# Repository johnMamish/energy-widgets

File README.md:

Framework / toolkit for making widgets powered by UI actions, focused on example applications.

Key points:

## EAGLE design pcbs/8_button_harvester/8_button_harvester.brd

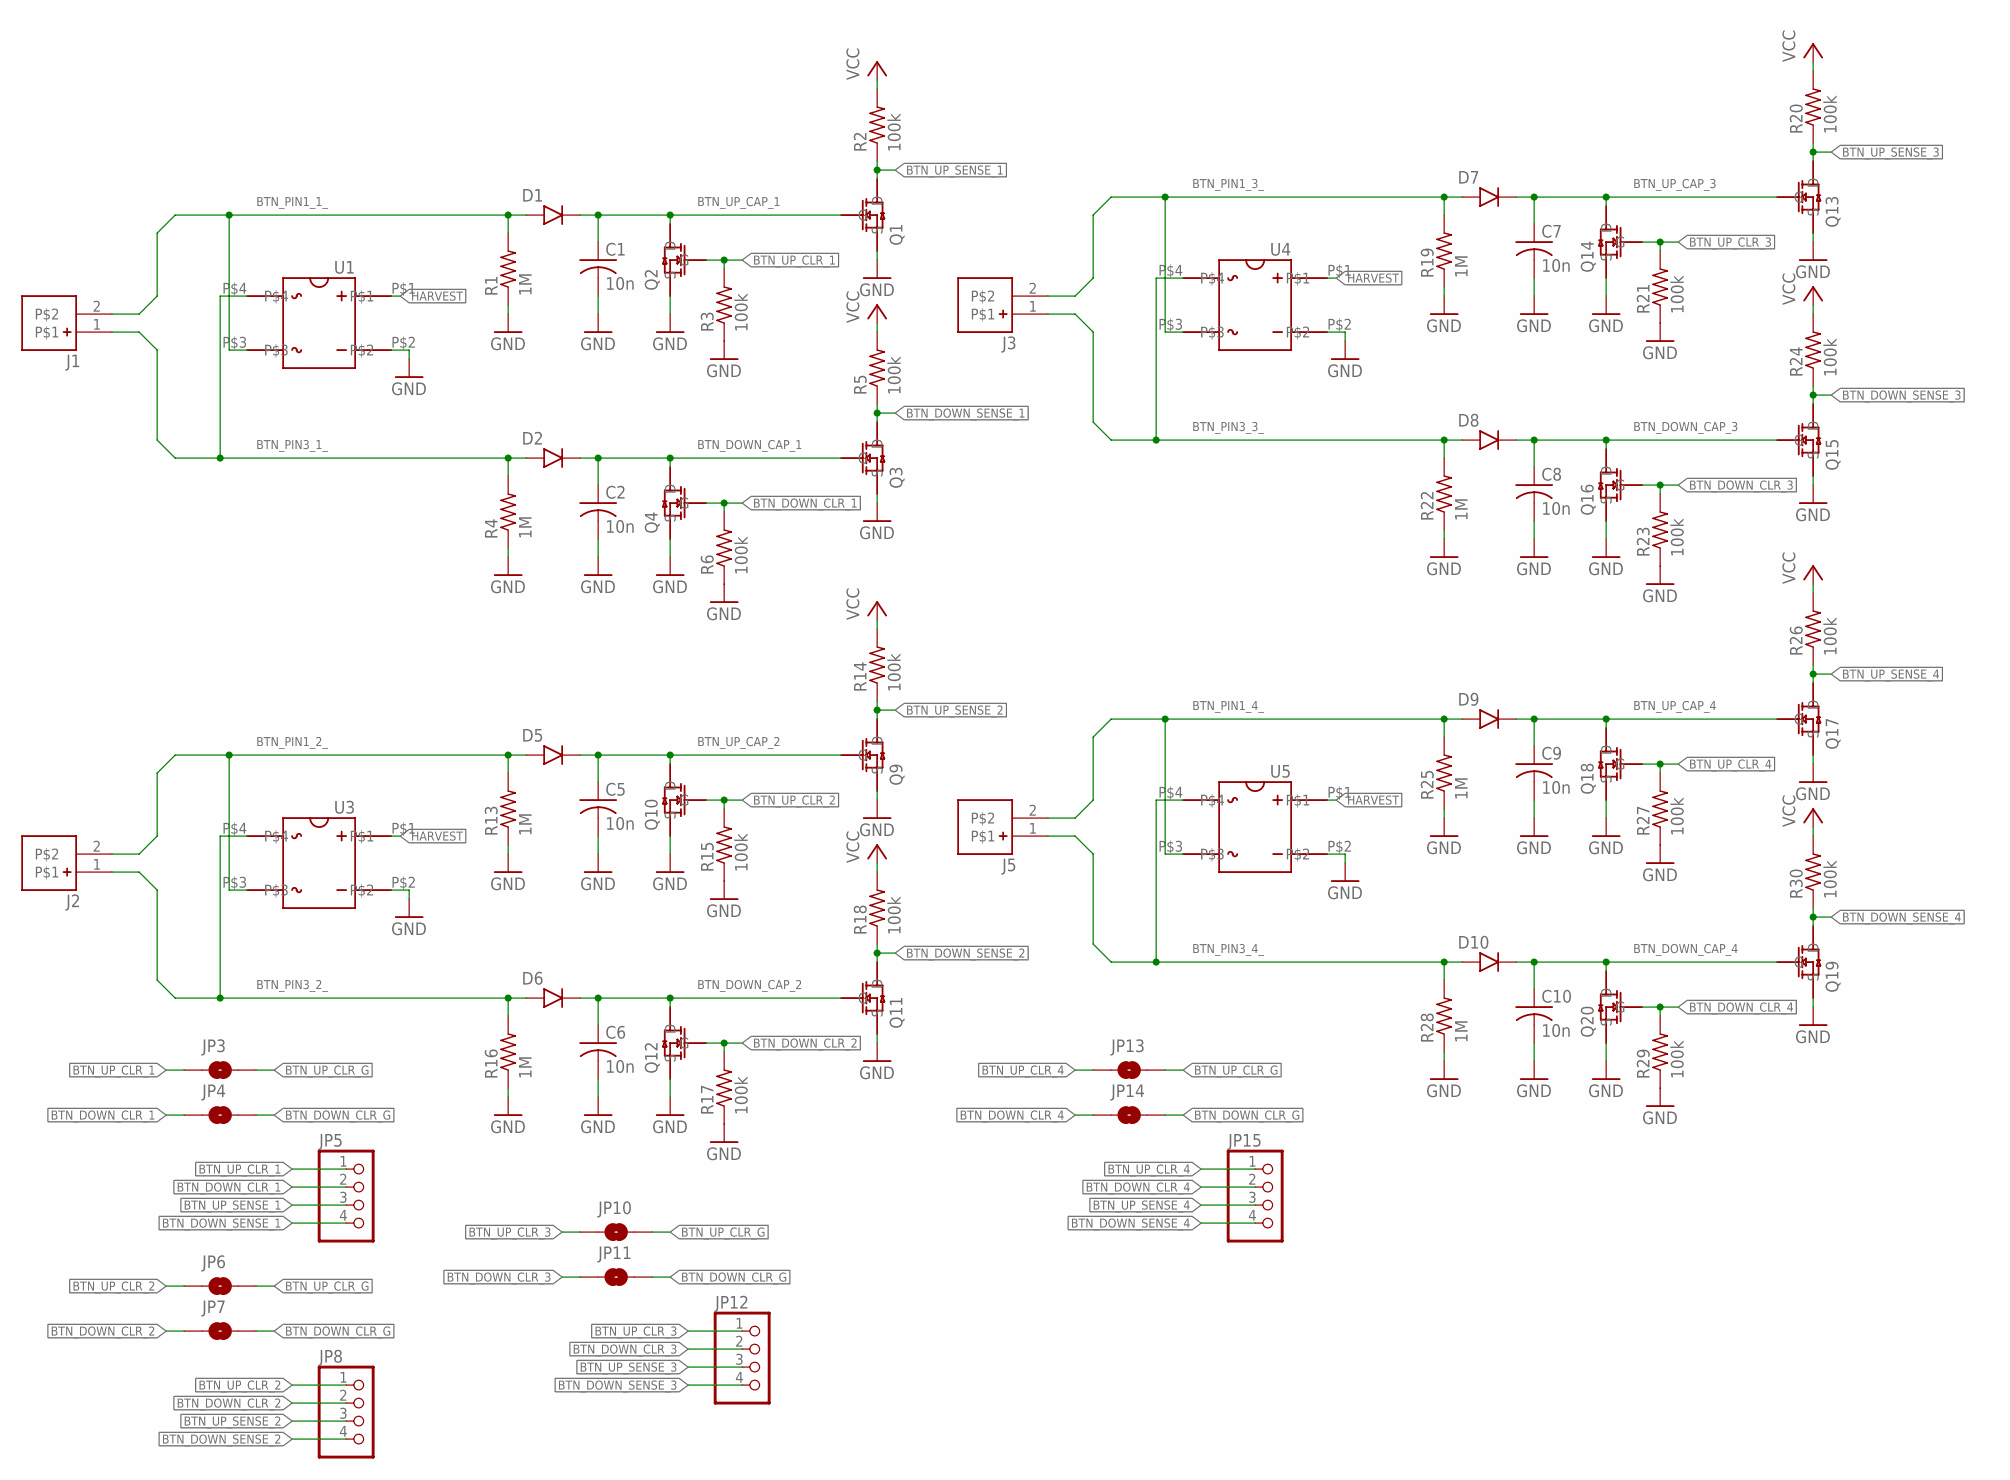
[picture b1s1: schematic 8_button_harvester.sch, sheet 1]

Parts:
C1, C2, C5, C6, C7, C8, C9, C10: 10n; C0402
D1, D2, D5, D6, D7, D8, D9, D10: DFLU1200
J1, J2, J3, J5: S2B-PH-SM4-TB
JP3, JP4, JP6, JP7, JP10, JP11, JP13, JP14: JUMPER-SMT_2_NO_NO-SILK; SMT-JUMPER_2_NO_NO-SILK
JP5, JP8, JP12, JP15: PINHD-1X4; 1X04
Q1, Q3, Q9, Q11, Q13, Q15, Q17, Q19: 2N7002K-7
Q2, Q4, Q10, Q12, Q14, Q16, Q18, Q20: BSS138K
R1, R4, R13, R16, R19, R22, R25, R28: 1M; R0402
R2, R3, R5, R6, R14, R15, R17, R18, R20, R21, R23, R24, R26, R27, R29, R30: 100k; R0402
U1, U3, U4, U5: CDBHD140L-G; CDBHDXX0L-G

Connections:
BTN_DOWN_CAP_1: C2.1, D2.K, Q3.G, Q4.D
BTN_DOWN_CAP_2: C6.1, D6.K, Q11.G, Q12.D
BTN_DOWN_CAP_3: C8.1, D8.K, Q15.G, Q16.D
BTN_DOWN_CAP_4: C10.1, D10.K, Q19.G, Q20.D
BTN_DOWN_CLR_1: JP4.1, JP5.2, Q4.G, R6.2
BTN_DOWN_CLR_2: JP7.1, JP8.2, Q12.G, R17.2
BTN_DOWN_CLR_3: JP11.1, JP12.2, Q16.G, R23.2
BTN_DOWN_CLR_4: JP14.1, JP15.2, Q20.G, R29.2
BTN_DOWN_CLR_G: JP4.2, JP7.2, JP11.2, JP14.2; also elsewhere on the board
BTN_DOWN_SENSE_1: JP5.4, Q3.D, R5.1
BTN_DOWN_SENSE_2: JP8.4, Q11.D, R18.1
BTN_DOWN_SENSE_3: JP12.4, Q15.D, R24.1
BTN_DOWN_SENSE_4: JP15.4, Q19.D, R30.1
BTN_PIN1_1_: D1.A, J1.2, R1.2, U1.P$3
BTN_PIN1_2_: D5.A, J2.2, R13.2, U3.P$3
BTN_PIN1_3_: D7.A, J3.2, R19.2, U4.P$3
BTN_PIN1_4_: D9.A, J5.2, R25.2, U5.P$3
BTN_PIN3_1_: D2.A, J1.1, R4.2, U1.P$4
BTN_PIN3_2_: D6.A, J2.1, R16.2, U3.P$4
BTN_PIN3_3_: D8.A, J3.1, R22.2, U4.P$4
BTN_PIN3_4_: D10.A, J5.1, R28.2, U5.P$4
BTN_UP_CAP_1: C1.1, D1.K, Q1.G, Q2.D
BTN_UP_CAP_2: C5.1, D5.K, Q9.G, Q10.D
BTN_UP_CAP_3: C7.1, D7.K, Q13.G, Q14.D
BTN_UP_CAP_4: C9.1, D9.K, Q17.G, Q18.D
BTN_UP_CLR_1: JP3.1, JP5.1, Q2.G, R3.2
BTN_UP_CLR_2: JP6.1, JP8.1, Q10.G, R15.2
BTN_UP_CLR_3: JP10.1, JP12.1, Q14.G, R21.2
BTN_UP_CLR_4: JP13.1, JP15.1, Q18.G, R27.2
BTN_UP_CLR_G: JP3.2, JP6.2, JP10.2, JP13.2; also elsewhere on the board
BTN_UP_SENSE_1: JP5.3, Q1.D, R2.1
BTN_UP_SENSE_2: JP8.3, Q9.D, R14.1
BTN_UP_SENSE_3: JP12.3, Q13.D, R20.1
BTN_UP_SENSE_4: JP15.3, Q17.D, R26.1
GND: C1.2, C2.2, C5.2, C6.2, C7.2, C8.2, C9.2, C10.2, Q1.S, Q2.S, Q3.S, Q4.S, Q9.S, Q10.S, Q11.S, Q12.S, Q13.S, Q14.S, Q15.S, Q16.S, Q17.S, Q18.S, Q19.S, Q20.S, R1.1, R3.1, R4.1, R6.1, R13.1, R15.1, R16.1, R17.1, R19.1, R21.1, R22.1, R23.1, R25.1, R27.1, R28.1, R29.1, U1.P$2, U3.P$2, U4.P$2, U5.P$2; also elsewhere on the board
HARVEST: U1.P$1, U3.P$1, U4.P$1, U5.P$1; also elsewhere on the board
VCC: R2.2, R5.2, R14.2, R18.2, R20.2, R24.2, R26.2, R30.2; also elsewhere on the board

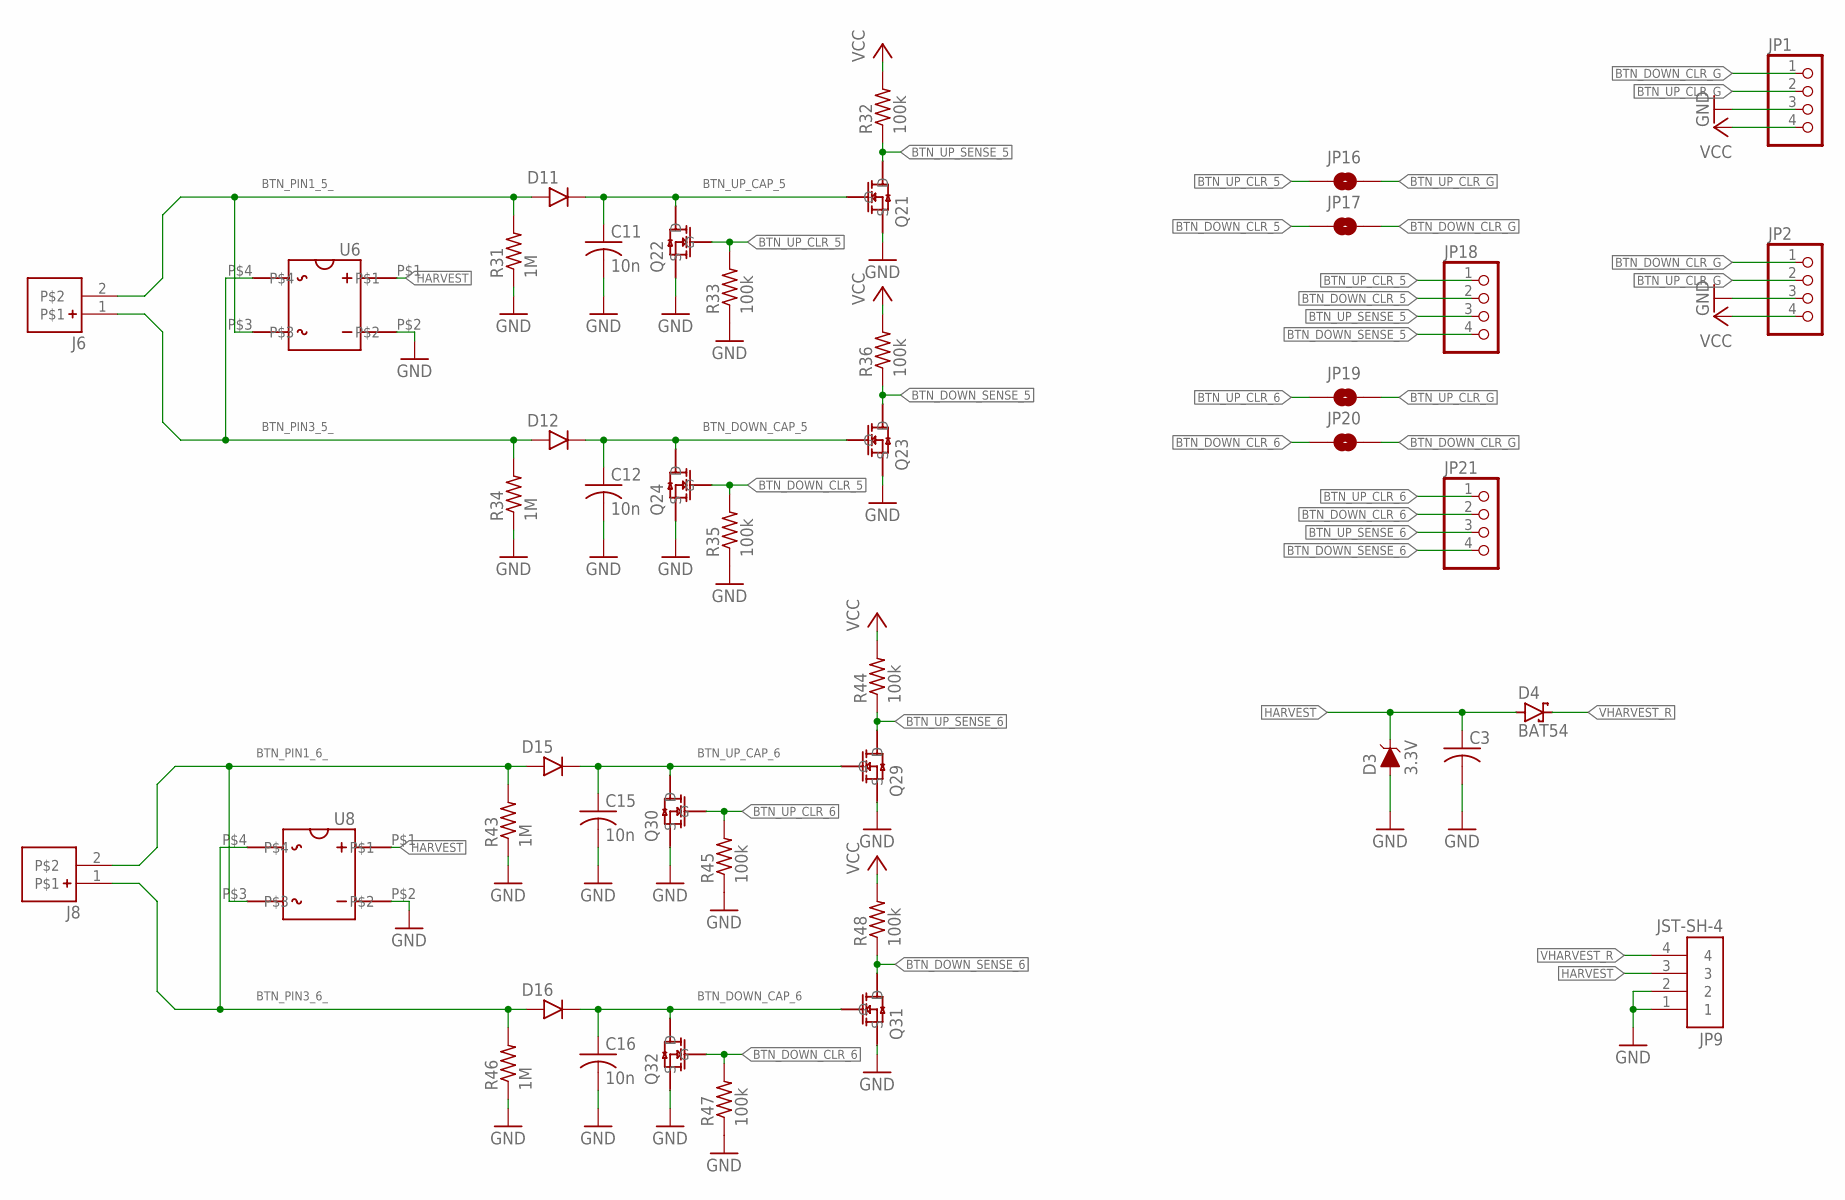
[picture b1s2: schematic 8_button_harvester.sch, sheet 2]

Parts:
C3: C-USC0805; C0805
C11, C12, C15, C16: 10n; C0402
D3: 3.3V; SOD-323
D4: BAT54; SOT23
D11, D12, D15, D16: DFLU1200
J6, J8: S2B-PH-SM4-TB
JP1, JP2, JP18, JP21: PINHD-1X4; 1X04
JP9: JST-SH-4
JP16, JP17, JP19, JP20: JUMPER-SMT_2_NO_NO-SILK; SMT-JUMPER_2_NO_NO-SILK
Q21, Q23, Q29, Q31: 2N7002K-7
Q22, Q24, Q30, Q32: BSS138K
R31, R34, R43, R46: 1M; R0402
R32, R33, R35, R36, R44, R45, R47, R48: 100k; R0402
U6, U8: CDBHD140L-G; CDBHDXX0L-G

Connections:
BTN_DOWN_CAP_5: C12.1, D12.K, Q23.G, Q24.D
BTN_DOWN_CAP_6: C16.1, D16.K, Q31.G, Q32.D
BTN_DOWN_CLR_5: JP17.1, JP18.2, Q24.G, R35.2
BTN_DOWN_CLR_6: JP20.1, JP21.2, Q32.G, R47.2
BTN_DOWN_CLR_G: JP1.1, JP2.1, JP17.2, JP20.2; also elsewhere on the board
BTN_DOWN_SENSE_5: JP18.4, Q23.D, R36.1
BTN_DOWN_SENSE_6: JP21.4, Q31.D, R48.1
BTN_PIN1_5_: D11.A, J6.2, R31.2, U6.P$3
BTN_PIN1_6_: D15.A, J8.2, R43.2, U8.P$3
BTN_PIN3_5_: D12.A, J6.1, R34.2, U6.P$4
BTN_PIN3_6_: D16.A, J8.1, R46.2, U8.P$4
BTN_UP_CAP_5: C11.1, D11.K, Q21.G, Q22.D
BTN_UP_CAP_6: C15.1, D15.K, Q29.G, Q30.D
BTN_UP_CLR_5: JP16.1, JP18.1, Q22.G, R33.2
BTN_UP_CLR_6: JP19.1, JP21.1, Q30.G, R45.2
BTN_UP_CLR_G: JP1.2, JP2.2, JP16.2, JP19.2; also elsewhere on the board
BTN_UP_SENSE_5: JP18.3, Q21.D, R32.1
BTN_UP_SENSE_6: JP21.3, Q29.D, R44.1
GND: C3.2, C11.2, C12.2, C15.2, C16.2, D3.A, JP1.3, JP2.3, JP9.1, JP9.2, Q21.S, Q22.S, Q23.S, Q24.S, Q29.S, Q30.S, Q31.S, Q32.S, R31.1, R33.1, R34.1, R35.1, R43.1, R45.1, R46.1, R47.1, U6.P$2, U8.P$2; also elsewhere on the board
HARVEST: C3.1, D3.C, D4.1 (A), JP9.3, U6.P$1, U8.P$1; also elsewhere on the board
VCC: JP1.4, JP2.4, R32.2, R36.2, R44.2, R48.2; also elsewhere on the board
VHARVEST_R: D4.3 (C), JP9.4

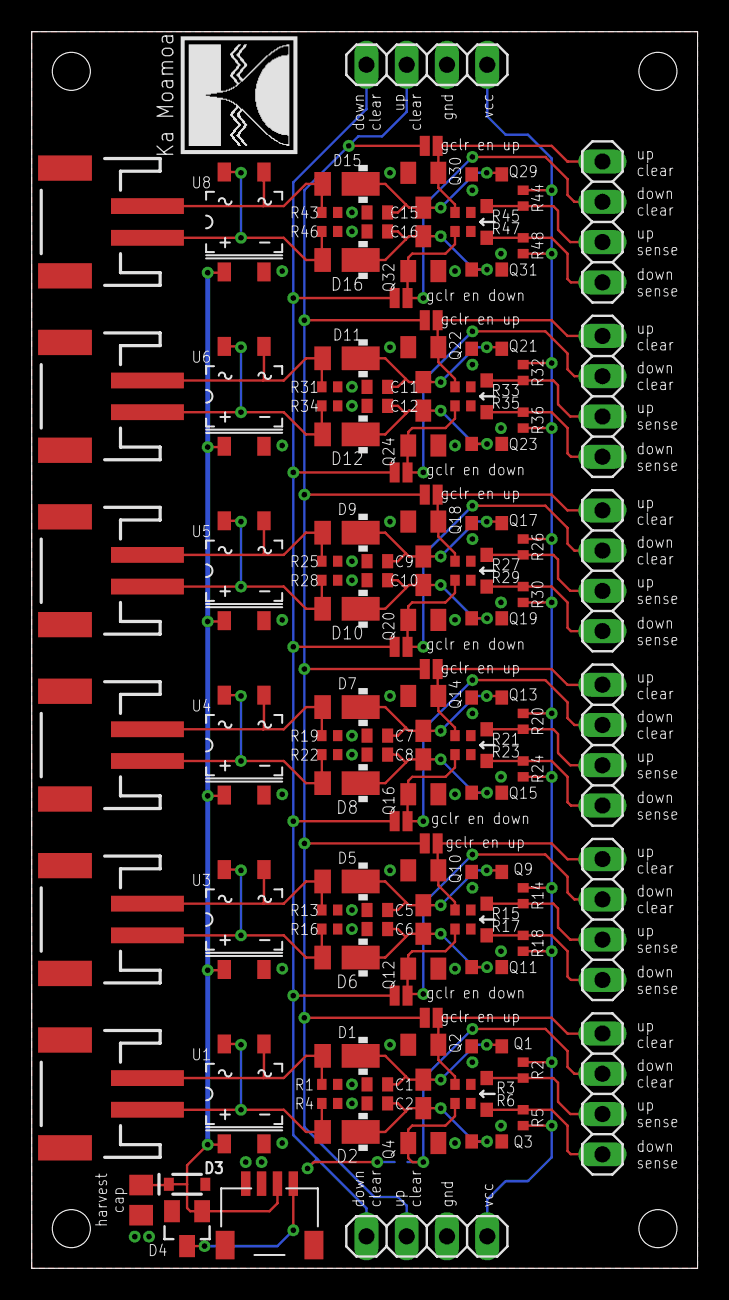
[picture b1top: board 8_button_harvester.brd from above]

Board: 2 copper layers, 42.0 x 78.0 mm, 120 parts (1 on the bottom side), 54 nets.

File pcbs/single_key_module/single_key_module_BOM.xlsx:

Digikey P/N | Manufacturer P/N | Quantity | Reference designator | Value | Device | Package | Description
 | N/A | 1 | AF1 | BUTTON-MOUNT | BUTTON-MOUNT | BUTTON-MOUNT
 | AFIG-0007 | 1
 | 878580002 | 1
 | C0402C103J3RACTU | 2 | C1, C2 | 10n | C-USC0402 | C0402 | CAPACITOR, American symbol
 | DFLU1200 | 2 | D1, D2 |  | DFLU1200 | DFLU1200
 | 61300411121 | 2 | headers |  |  |  | PIN HEADER
 | 2N7002K-7 | 2 | Q1, Q3 | 2N7002K-7 | 2N7002K-7 | 2N7002K-7
 | BSS138K | 2 | Q2, Q4 | BSS138K | BSS138K | BSS138K
 | ERJ-2GEJ105X | 2 | R1, R4 | 1M | R-US_R0402 | R0402 | RESISTOR, American symbol
 | ERJ-2GEJ104X | 4 | R2, R3, R5, R6 | 100k | R-US_R0402 | R0402 | RESISTOR, American symbol
 | CDBHD140L-G | 1 | U1 | CDBHD140L-G | CDBHD140L-G | CDBHDXX0L-G

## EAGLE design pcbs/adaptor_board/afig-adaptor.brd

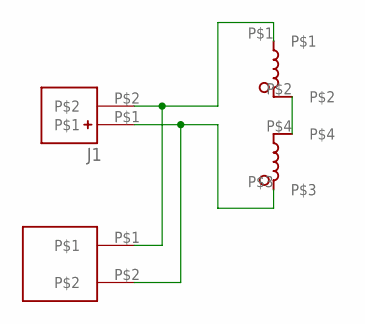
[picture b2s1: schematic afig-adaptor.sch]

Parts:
J1: B2B-PH-SM4-TB
U$1: AFIG-0007
U$2: 0878580002

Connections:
unnamed: U$1.P$2, U$1.P$4
unnamed: J1.P$1, U$1.P$3, U$2.P$2
unnamed: J1.P$2, U$1.P$1, U$2.P$1

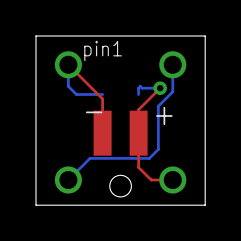
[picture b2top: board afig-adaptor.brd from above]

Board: 2 copper layers, 9.4 x 9.4 mm, 3 parts (1 on the bottom side), 3 nets.

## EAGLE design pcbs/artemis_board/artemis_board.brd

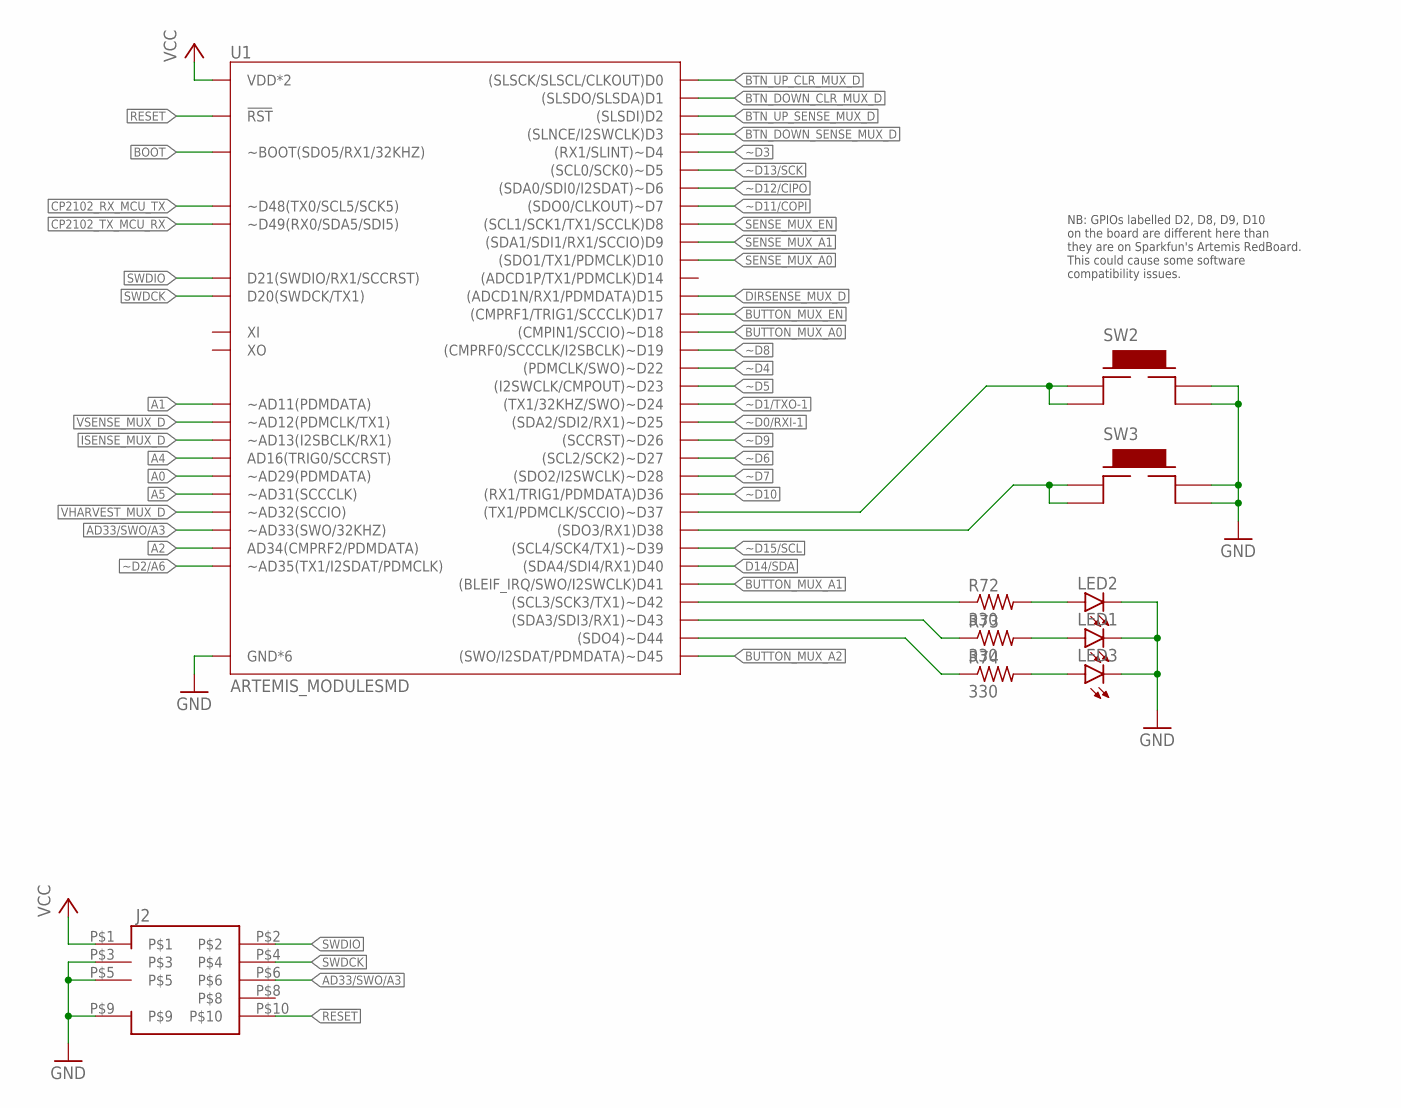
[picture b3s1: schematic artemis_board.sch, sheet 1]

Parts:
J2: FTSH-105-01-F-DV-007-K-P
LED1, LED2, LED3: LEDCHIP-LED0603; CHIP-LED0603; MFR_PN BR1111C-TR
R72, R73, R74: 330; R0402; MFR_PN RC0402FR-07330RL
SW2, SW3: TE_FSM4JSMA; TE_FSMJSMA
U1: ARTEMIS_MODULESMD; ARTEMIS_FP; MFR_PN WRL-15484

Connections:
!RESET: J2.P$10, U1.~RST (!RST); also elsewhere on the board
A0: U1.~AD29 (~AD29(PDMDATA)); also elsewhere on the board
A1: U1.~AD11 (~AD11(PDMDATA)); also elsewhere on the board
A2: U1.AD34 (AD34(CMPRF2/PDMDATA)); also elsewhere on the board
A4: U1.AD16 (AD16(TRIG0/SCCRST)); also elsewhere on the board
A5: U1.~AD31 (~AD31(SCCCLK)); also elsewhere on the board
AD33/SWO/A3: J2.P$6, U1.~AD33/SWO (~AD33(SWO/32KHZ)); also elsewhere on the board
BOOT: U1.BOOT (~BOOT(SDO5/RX1/32KHZ)); also elsewhere on the board
BTN_DOWN_CLR_MUX_D: U1.D1 ((SLSDO/SLSDA)D1); also elsewhere on the board
BTN_DOWN_SENSE_MUX_D: U1.D3 ((SLNCE/I2SWCLK)D3); also elsewhere on the board
BTN_UP_CLR_MUX_D: U1.D0 ((SLSCK/SLSCL/CLKOUT)D0); also elsewhere on the board
BTN_UP_SENSE_MUX_D: U1.D2 ((SLSDI)D2); also elsewhere on the board
BUTTON_MUX_A0: U1.~D18 ((CMPIN1/SCCIO)~D18); also elsewhere on the board
BUTTON_MUX_A1: U1.D41 ((BLEIF_IRQ/SWO/I2SWCLK)D41); also elsewhere on the board
BUTTON_MUX_A2: U1.~D45 ((SWO/I2SDAT/PDMDATA)~D45); also elsewhere on the board
BUTTON_MUX_EN: U1.D17 ((CMPRF1/TRIG1/SCCCLK)D17); also elsewhere on the board
CP2102_RX_MCU_TX: U1.TXO-0 (~D48(TX0/SCL5/SCK5)); also elsewhere on the board
CP2102_TX_MCU_RX: U1.RXI-0 (~D49(RX0/SDA5/SDI5)); also elsewhere on the board
D14/SDA: U1.D40 ((SDA4/SDI4/RX1)D40); also elsewhere on the board
DIRSENSE_MUX_D: U1.D15 ((ADCD1N/RX1/PDMDATA)D15); also elsewhere on the board
GND: J2.P$3, J2.P$5, J2.P$9, LED1.C, LED2.C, LED3.C, SW2.P$3, SW2.P$4, SW3.P$3, SW3.P$4, U1.GND@1 (GND*6), U1.GND@22 (GND*6), U1.GND@38 (GND*6), U1.GND@39 (GND*6), U1.GND@47 (GND*6), U1.GND@59 (GND*6); also elsewhere on the board
ISENSE_MUX_D: U1.~AD13 (~AD13(I2SBCLK/RX1)); also elsewhere on the board
unnamed: R72.1, U1.~D42 ((SCL3/SCK3/TX1)~D42)
unnamed: R73.1, U1.~D43 ((SDA3/SDI3/RX1)~D43)
unnamed: R74.1, U1.~D44 ((SDO4)~D44)
unnamed: LED2.A, R72.2
unnamed: LED1.A, R73.2
unnamed: LED3.A, R74.2
unnamed: SW2.P$1, SW2.P$2, U1.~D37 ((TX1/PDMCLK/SCCIO)~D37)
unnamed: SW3.P$1, SW3.P$2, U1.D38 ((SDO3/RX1)D38)
SENSE_MUX_A0: U1.D10 ((SDO1/TX1/PDMCLK)D10); also elsewhere on the board
SENSE_MUX_A1: U1.D9 ((SDA1/SDI1/RX1/SCCIO)D9); also elsewhere on the board
SENSE_MUX_EN: U1.D8 ((SCL1/SCK1/TX1/SCCLK)D8); also elsewhere on the board
SWDCK: J2.P$4, U1.SWDCK (D20(SWDCK/TX1))
SWDIO: J2.P$2, U1.SWDIO (D21(SWDIO/RX1/SCCRST))
VCC: J2.P$1, U1.VDD@36 (VDD*2), U1.VDD@37 (VDD*2); also elsewhere on the board
VHARVEST_MUX_D: U1.~AD32 (~AD32(SCCIO)); also elsewhere on the board
VSENSE_MUX_D: U1.~AD12 (~AD12(PDMCLK/TX1)); also elsewhere on the board
~D0/RXI-1: U1.~D25 ((SDA2/SDI2/RX1)~D25); also elsewhere on the board
~D1/TXO-1: U1.~D24 ((TX1/32KHZ/SWO)~D24); also elsewhere on the board
~D2/A6: U1.~AD35 (~AD35(TX1/I2SDAT/PDMCLK)); also elsewhere on the board
~D3: U1.~D4 ((RX1/SLINT)~D4); also elsewhere on the board
~D4: U1.~D22 ((PDMCLK/SWO)~D22); also elsewhere on the board
~D5: U1.~D23 ((I2SWCLK/CMPOUT)~D23); also elsewhere on the board
~D6: U1.~D27 ((SCL2/SCK2)~D27); also elsewhere on the board
~D7: U1.~D28 ((SDO2/I2SWCLK)~D28); also elsewhere on the board
~D8: U1.~D19 ((CMPRF0/SCCCLK/I2SBCLK)~D19); also elsewhere on the board
~D9: U1.~D26 ((SCCRST)~D26); also elsewhere on the board
~D10: U1.D36 ((RX1/TRIG1/PDMDATA)D36); also elsewhere on the board
~D11/COPI: U1.D7 ((SDO0/CLKOUT)~D7); also elsewhere on the board
~D12/CIPO: U1.~D6 ((SDA0/SDI0/I2SDAT)~D6); also elsewhere on the board
~D13/SCK: U1.~D5 ((SCL0/SCK0)~D5); also elsewhere on the board
~D15/SCL: U1.~D39 ((SCL4/SCK4/TX1)~D39); also elsewhere on the board

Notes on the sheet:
NB: GPIOs labelled D2, D8, D9, D10 on the board are different here than they are on Sparkfun's Artemis RedBoard. This could cause some software compatibility issues.

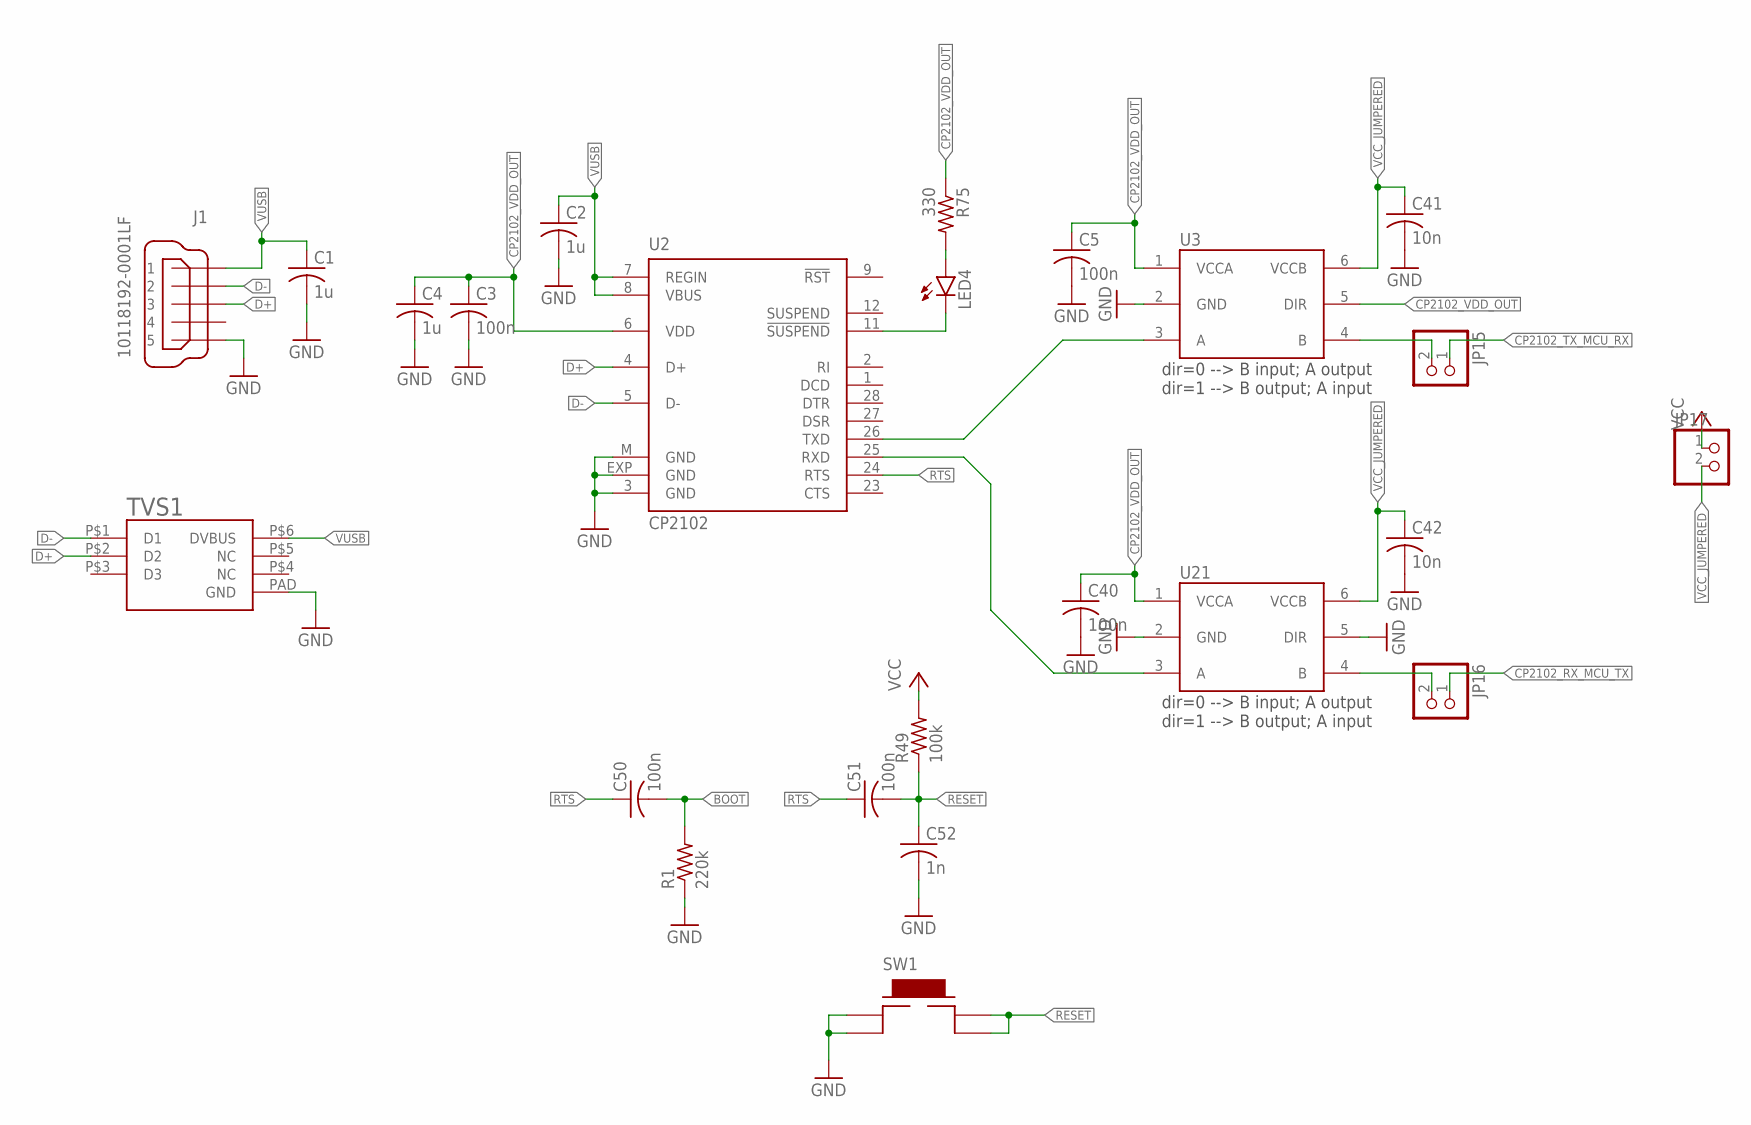
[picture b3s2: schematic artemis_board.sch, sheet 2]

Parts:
C1, C2, C4: 1u; C0402; MFR_PN CL05A105KO5NNNC
C3, C5, C40, C50, C51: 100n; C0402; MFR_PN CL05B104KO5NNNC
C41, C42: 10n; C0402; MFR_PN CL05B103KO5NNNC
C52: 1n; C0402; MFR_PN CL05B102KB5NNNC
J1: 10118192-0001LF
JP15, JP16, JP17: PINHD-1X2; 1X02
LED4: LEDCHIP-LED0603; CHIP-LED0603; MFR_PN BR1111C-TR
R1: 220k; R0402; MFR_PN RC0402FR-07220KL
R49: 100k; R0402; MFR_PN RC0402FR-07100KL
R75: 330; R0402; MFR_PN RC0402FR-07330RL
SW1: TE_FSM4JSMA; TE_FSMJSMA
TVS1: RCLAMP3654PAT; RCLAMP3654PATCT
U2: CP2102; MLP28; MFR_PN CP2102-GM
U3, U21: 74AXP1T45GWH; SOT65P210X110-6N

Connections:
!RESET: C51.2, C52.1, R49.1, SW1.P$3, SW1.P$4; also elsewhere on the board
!RTS: C50.1, C51.1, U2.24 (RTS)
BOOT: C50.2, R1.2; also elsewhere on the board
CP2102_RX_MCU_TX: JP16.1; also elsewhere on the board
CP2102_TX_MCU_RX: JP15.1; also elsewhere on the board
CP2102_VDD_OUT: C3.1, C4.1, C5.1, C40.1, R75.1, U2.6 (VDD), U3.1 (VCCA), U3.5 (DIR), U21.1 (VCCA)
D+: J1.3, TVS1.P$2 (D2), U2.4 (D+)
D-: J1.2, TVS1.P$1 (D1), U2.5 (D-)
GND: C1.2, C2.2, C3.2, C4.2, C5.2, C40.2, C41.2, C42.2, C52.2, J1.5, R1.1, SW1.P$1, SW1.P$2, TVS1.PAD (GND), U2.3 (GND), U2.EXP (GND), U2.M (GND), U3.2 (GND), U21.2 (GND), U21.5 (DIR); also elsewhere on the board
unnamed: LED4.A, R75.2
unnamed: JP15.2, U3.4 (B)
unnamed: JP16.2, U21.4 (B)
unnamed: LED4.C, U2.11 (!SUSPEND)
RXD_3V3: U2.25 (RXD), U21.3 (A)
TXD_3V3: U2.26 (TXD), U3.3 (A)
VCC: JP17.1, R49.2; also elsewhere on the board
VCC_JUMPERED: C41.1, C42.1, JP17.2, U3.6 (VCCB), U21.6 (VCCB)
VUSB: C1.1, C2.1, J1.1, TVS1.P$6 (DVBUS), U2.7 (REGIN), U2.8 (VBUS); also elsewhere on the board

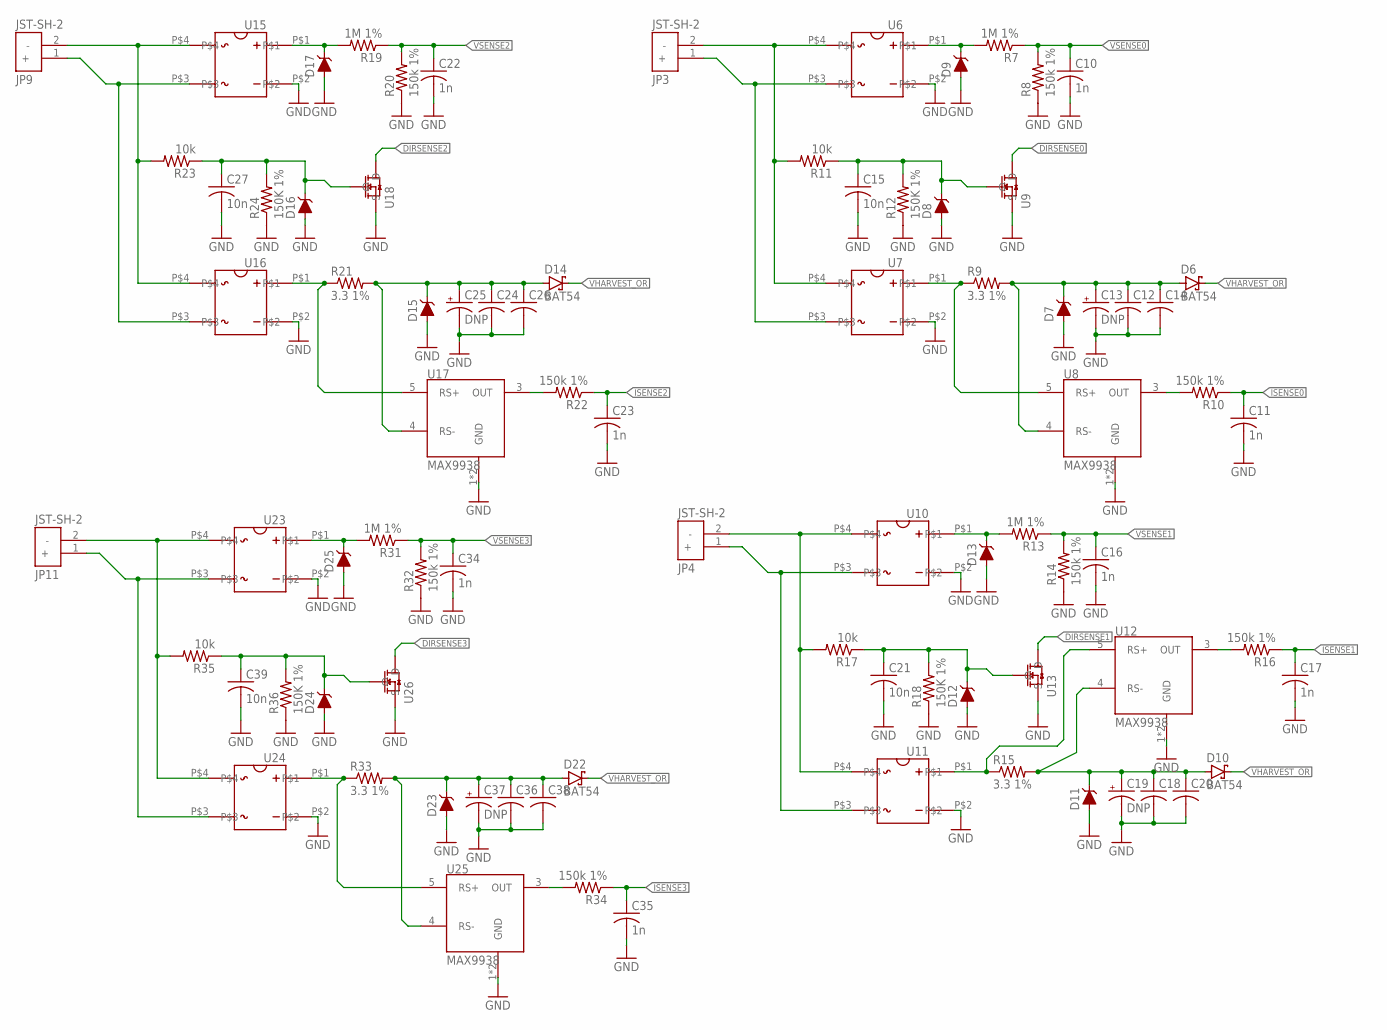
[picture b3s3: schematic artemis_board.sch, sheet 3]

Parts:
C10, C11, C16, C17, C22, C23, C34, C35: 1n; C0402; MFR_PN CL05B102KB5NNNC
C12, C14, C18, C20, C24, C26, C36, C38: C-USC1206; C1206; MFR_PN C3216X5R1E476M160AC
C13, C19, C25, C37: DNP; E2,5-5
C15, C21, C27, C39: 10n; C0402; MFR_PN CL05B103KB5NNNC
D6, D10, D14, D22: BAT54; SOT23; MFR_PN BAT54
D7, D8, D9, D11, D12, D13, D15, D16, D17, D23, D24, D25: 3.3V; SOD-323; MFR_PN BZT52C15S
JP3, JP4, JP9, JP11: JST-SH-2; MFR_PN SM02B-SRSS-TB(LF)(SN)
R7, R13, R19, R31: 1M 1%; R0402; MFR_PN RC0402FR-071ML
R8, R10, R14, R16, R20, R22, R32, R34: 150k 1%; R0402; MFR_PN RC0402FR-07150KL
R9, R15, R21, R33: 3.3 1%; R0603; MFR_PN ERJ-3BQF3R3V
R11, R17, R23, R35: 10k; R0402; MFR_PN RC0402FR-0710KL
R12, R18, R24, R36: 150K 1%; R0402; MFR_PN RC0402FR-07150KL
U6, U7, U10, U11, U15, U16, U23, U24: CDBHD140L-G; CDBHDXX0L-G; MFR_PN CDBHD140L-G
U8, U12, U17, U25: MAX9938; SOT23-5; MFR_PN MAX9938TEUK+T
U9, U13, U18, U26: TN2106K1-G

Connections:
DIRSENSE0: U9.D; also elsewhere on the board
DIRSENSE1: U13.D; also elsewhere on the board
DIRSENSE2: U18.D; also elsewhere on the board
DIRSENSE3: U26.D; also elsewhere on the board
GND: C10.2, C11.2, C12.2, C13.-, C14.2, C15.2, C16.2, C17.2, C18.2, C19.-, C20.2, C21.2, C22.2, C23.2, C24.2, C25.-, C26.2, C27.2, C34.2, C35.2, C36.2, C37.-, C38.2, C39.2, D7.A, D8.A, D9.A, D11.A, D12.A, D13.A, D15.A, D16.A, D17.A, D23.A, D24.A, D25.A, R8.1, R12.1, R14.1, R18.1, R20.1, R24.1, R32.1, R36.1, U6.P$2, U7.P$2, U8.1 (GND), U8.2 (GND), U9.S, U10.P$2, U11.P$2, U12.1 (GND), U12.2 (GND), U13.S, U15.P$2, U16.P$2, U17.1 (GND), U17.2 (GND), U18.S, U23.P$2, U24.P$2, U25.1 (GND), U25.2 (GND), U26.S; also elsewhere on the board
ISENSE0: C11.1, R10.1; also elsewhere on the board
ISENSE1: C17.1, R16.1; also elsewhere on the board
ISENSE2: C23.1, R22.1; also elsewhere on the board
ISENSE3: C35.1, R34.1; also elsewhere on the board
unnamed: JP3.2 (-), R11.2, U6.P$4, U7.P$4
unnamed: JP3.1 (+), U6.P$3, U7.P$3
unnamed: D9.C, R7.2, U6.P$1
unnamed: R9.1, U7.P$1, U8.5 (RS+)
unnamed: R10.2, U8.3 (OUT)
unnamed: C15.1, D8.C, R11.1, R12.2, U9.G
unnamed: JP4.2 (-), R17.2, U10.P$4, U11.P$4
unnamed: JP4.1 (+), U10.P$3, U11.P$3
unnamed: D13.C, R13.2, U10.P$1
unnamed: R15.1, U11.P$1, U12.5 (RS+)
unnamed: R16.2, U12.3 (OUT)
unnamed: C21.1, D12.C, R17.1, R18.2, U13.G
unnamed: JP9.2 (-), R23.2, U15.P$4, U16.P$4
unnamed: JP9.1 (+), U15.P$3, U16.P$3
unnamed: D17.C, R19.2, U15.P$1
unnamed: R21.1, U16.P$1, U17.5 (RS+)
unnamed: R22.2, U17.3 (OUT)
unnamed: C27.1, D16.C, R23.1, R24.2, U18.G
unnamed: JP11.2 (-), R35.2, U23.P$4, U24.P$4
unnamed: JP11.1 (+), U23.P$3, U24.P$3
unnamed: D25.C, R31.2, U23.P$1
unnamed: R33.1, U24.P$1, U25.5 (RS+)
unnamed: R34.2, U25.3 (OUT)
unnamed: C39.1, D24.C, R35.1, R36.2, U26.G
VHARVEST0: C12.1, C13.+, C14.1, D6.1 (A), D7.C, R9.2, U8.4 (RS-); also elsewhere on the board
VHARVEST1: C18.1, C19.+, C20.1, D10.1 (A), D11.C, R15.2, U12.4 (RS-); also elsewhere on the board
VHARVEST2: C24.1, C25.+, C26.1, D14.1 (A), D15.C, R21.2, U17.4 (RS-); also elsewhere on the board
VHARVEST3: C36.1, C37.+, C38.1, D22.1 (A), D23.C, R33.2, U25.4 (RS-); also elsewhere on the board
VHARVEST_OR: D6.3 (C), D10.3 (C), D14.3 (C), D22.3 (C); also elsewhere on the board
VSENSE0: C10.1, R7.1, R8.2; also elsewhere on the board
VSENSE1: C16.1, R13.1, R14.2; also elsewhere on the board
VSENSE2: C22.1, R19.1, R20.2; also elsewhere on the board
VSENSE3: C34.1, R31.1, R32.2; also elsewhere on the board

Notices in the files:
parts and their libraries:
SparkFun-DiscreteSemi: Licensing: Creative Commons ShareAlike 4.0 International - https://creativecommons.org/licenses/by-sa/4.0
